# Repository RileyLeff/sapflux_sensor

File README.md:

# Sap Flux Logic Board

An open hardware logic board for experimental heat-pulse sap flux sensors.

Sap flux sensors estimate how water moves through trees by watching heat move
through sapwood. Current sensors are expensive, power-hungry, and not all that accurate.

This repo contains some hardware I'm developing to fix all of that stuff!

## Current Status

The board is real and in-hand. The first revision literally exploded on power-on because I did not know the convention for communicating diode orientation to JLCPCB.

The repo now contains a second revision of the board with some minor improvements to the power layout, and I did not bork the layout confirmation on the second order. The board is working great in the lab!

So far, the beauty and splendor promised in the simulations seems to transfer to real-world situations. I've seen enough to make me confident that:

1. The new measurement theory works, and crushes the old theory. I'm presenting on this at AGU in December 2026!
2. The logic board design works. I don't think it's fully optimal/ready-to-scale yet, but my initial lab testing has convinced me it's sound.

I'll link to my data and AGU presentation when I have them ready for public consumption. In the meantime, you're welcome to check out the hardware here in this repo.

I haven't yet fully deployed in real field conditions, and I imagine there will be some empirical caveats and gotchas to navigate in those deployments. But so far so good!

The main thing to figure out from here is basically: now that we can actually inference the sap flux model accurately, are there variable, empirical features of the measurement that we can solve with better theory or engineering? Empiricism on plants is hard: they're complicated and diverse. The less empiricism we have to do on our estimates, the higher our bandwidth gets.

## What's Going On In Here?

Want to measure how fast water moves through a tree at high frequency? It's useful to know because it connects a tree to nearly all of its environmental conditions. We have a model to measure this and a sensor to provide data for it, but our model is broken in two specific ways:

- The actual probes in the tree get slightly misaligned when you install them, and tiny misalignments produce mega-huge errors.
- The probes work by introducing a heat pulse into the tree and measuring how fast it moves. How much of that movement is attributable to convection (sap flux) versus conduction? Current implementations attribute all variation to convection, which is a bad assumption.

The first problem is massive in magnitude. The second one is smaller (convection does genuinely change more than conduction) but more destructive per unit error because it's deeply confounded with stuff on the tree that you actually want to measure, like water potential or wood density.

This is open hardware that allows me to test my newly derived method for inferring sap flux rates from the raw data: we can't use commercial sensors because they're locked down and they discard most of the raw signal in favor of restrictive summary statistics. I do have a separate project that decompresses those summary statistics into distributions of possible raw measurements, but it's better to just keep the data in the first place.

Since we're already in the business of building custom hardware, we can get the power consumption down and the costs down as well.

## What The Board Does

Here are some design notes:

- 48 thermistor channels through three analog multiplexers.
- One ADS1115 ADC for heat-pulse temperature traces and excitation sensing.
- Support for analog sensor heads with internal 10k half-bridge thermistor setups.
- Shorter, higher-power heat pulses (which flatten out the signal less).
- Up to 120W power output in very short bursts across 8 sensors with ~40-45 ohm heater resistance.
- 24V field power input with protection and a 3.3V buck supply.
- RS-485.
- 32 MB SPI flash.
- I2C EEPROM.
- STM32G0B1 microcontroller target, intended for embedded Rust firmware with
  the [Embassy](https://github.com/embassy-rs/embassy) framework.
- Six layers, KiCad layout, fabbed at JLC.

I put a fairly complex analog mechanism for shutting down the heater on here because I'm worried about the case where a broken sensor in a dead tree starts a forest fire. This is probably the area that could use the most simplification in future revisions. Right now it mostly serves to annoyingly latch my heater shut by accident if the power supply ever blips in a way that the power shutdown doesn't like. I've made some firmware improvements for handling it, but I think the hardware could be improved there.

## Compared With Current Workflows

This one:
- Open, hackable
- <1mW idle power consumption (if you're creative with shutting off the RS-485 transceiver, e.g., a 15-second polling interval)
- Maybe $50/board at small/medium volumes, $20/board at large volumes

Commercial:
- Closed
- \>100mW idle power consumption
- $1000/sensor + $1000+ logger
- More expensive infrastructure to support the greater power consumption

I don't think this is the final sensor topology, but 8x analog sensor heads per board is really nice for testing the method in the lab. I figure I'll make a more integrated, more deployment-friendly design in the future.

## Reproducibility

Atopile is the canonical electrical design source for this board:

- [`elec/main.ato`](elec/main.ato)
- [`elec/ato.yaml`](elec/ato.yaml)
- [`elec/`](elec/)

Note that I found it *really nice* to work with Claude via atopile! I'm still doing the layout by hand, but putting the electrical connectivity in a Python-like language made iteration and review a breeze.

Same with the PCBParts MCP server. I always found navigating parts to be a big barrier between me, the inexperienced hardware fan that fools around with breadboards sometimes, and building a PCB from scratch. Claude is really good at that stuff if you provide good tools.

The KiCad layout is here:

- [`elec/layouts/default/default.kicad_pcb`](elec/layouts/default/default.kicad_pcb)

The shipped fabrication packages are frozen here:

- v0.2 (current, working board): [`releases/sap-flux-adapter-v0.2-2026-06-26/`](releases/sap-flux-adapter-v0.2-2026-06-26/)
- v0.1 (first board; the folder name says v1.1, but the board itself is labeled v0.1): [`releases/sap-flux-adapter-v1.1-shipped-2026-03-21/`](releases/sap-flux-adapter-v1.1-shipped-2026-03-21/)

For more detail, see [`docs/reproducibility.md`](docs/reproducibility.md). Note that it's a Claude-written document. I suggest pointing your LLM agent at the repo to inspect the guts of it. This README is written by hand (by Riley) but the rest of the repo is a Claude party.

## Internal Links (Claude's Docs)

- Specs: [`docs/specs.md`](docs/specs.md)
- Reproducibility notes: [`docs/reproducibility.md`](docs/reproducibility.md)
- Design history: [`docs/design-history/`](docs/design-history/)
- Shipped releases: [v0.2](releases/sap-flux-adapter-v0.2-2026-06-26/), [v0.1](releases/sap-flux-adapter-v1.1-shipped-2026-03-21/)

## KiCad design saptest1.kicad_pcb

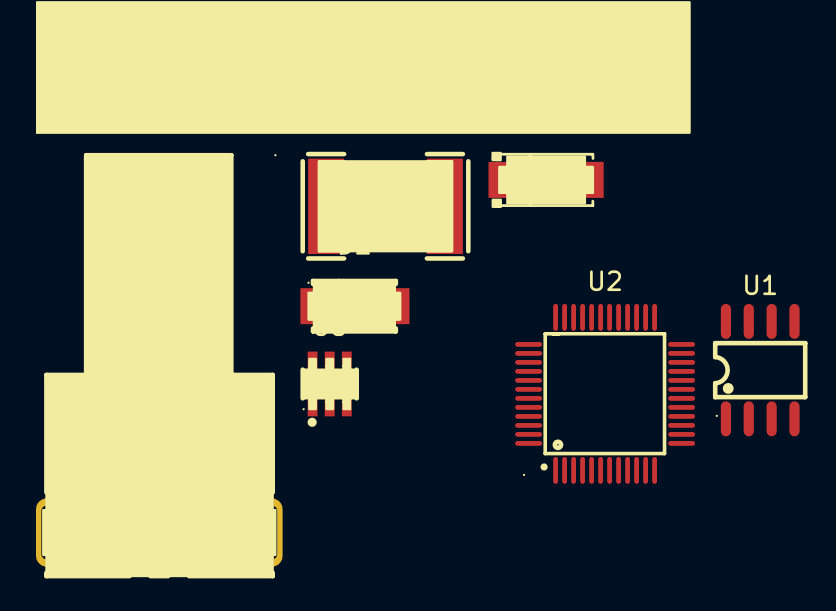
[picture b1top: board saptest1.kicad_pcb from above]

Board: 2 copper layers, 8 parts (0 on the bottom side), 4 nets, no tracks yet.

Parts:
D1: SS36; SMA_L4.3-W2.6-LS5.2-RD
D2: SMAJ30A_C698947; SMA_L4.5-W2.6-LS5.1-RD
F1: 2920L110/60MR; F2920
J1: M8-P4A-GPL_M8-JD; CONN-TH_M8-P4A-GPL-M8-JD
U1: CAT24C32WI-GT3; SOIC-8_L5.0-W4.0-P1.27-LS6.0-BL
U2: STM32G0B1CBT6; LQFP-48_L7.0-W7.0-P0.50-LS9.0-BL
U3: KF2EDGV-3_5-10P; CONN-TH_10P-P3.50_KF2EDGV-3.5-10P
U5: LMR14006YDDCR; TSOT-23-6_L2.9-W1.6-P0.95-LS2.8-BL

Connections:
+24V Protected: D1.1 (K), D2.1
GND: D2.2, J1.3
unnamed: D1.2 (A), F1.2
unnamed: F1.1, J1.1

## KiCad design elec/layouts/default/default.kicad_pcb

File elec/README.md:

# Sap Flux Adapter Electronics

This directory contains the Atopile source for the sap flux adapter board.
Atopile is the canonical electrical design for the shipped prototype.

## Entry Point

- `main.ato` defines the top-level `SapFluxAdapter` module.
- `ato.yaml` defines the `default` build.
- `layouts/default/default.kicad_pcb` is the hand-routed KiCad layout that was
  fabricated by JLCPCB.

## Build

```bash
ato build
```

Run from this directory.

Be careful with rebuilds: the KiCad PCB includes hand placement, routing,
board-art, and late manufacturing fixes. For the board that was physically
fabricated, use the frozen release package in
`../releases/sap-flux-adapter-v1.1-shipped-2026-03-21/`.

## Tooling

This design was built with Atopile and KiCad. `pcbparts` was used heavily for
part discovery and package/footprint work while learning hardware design.

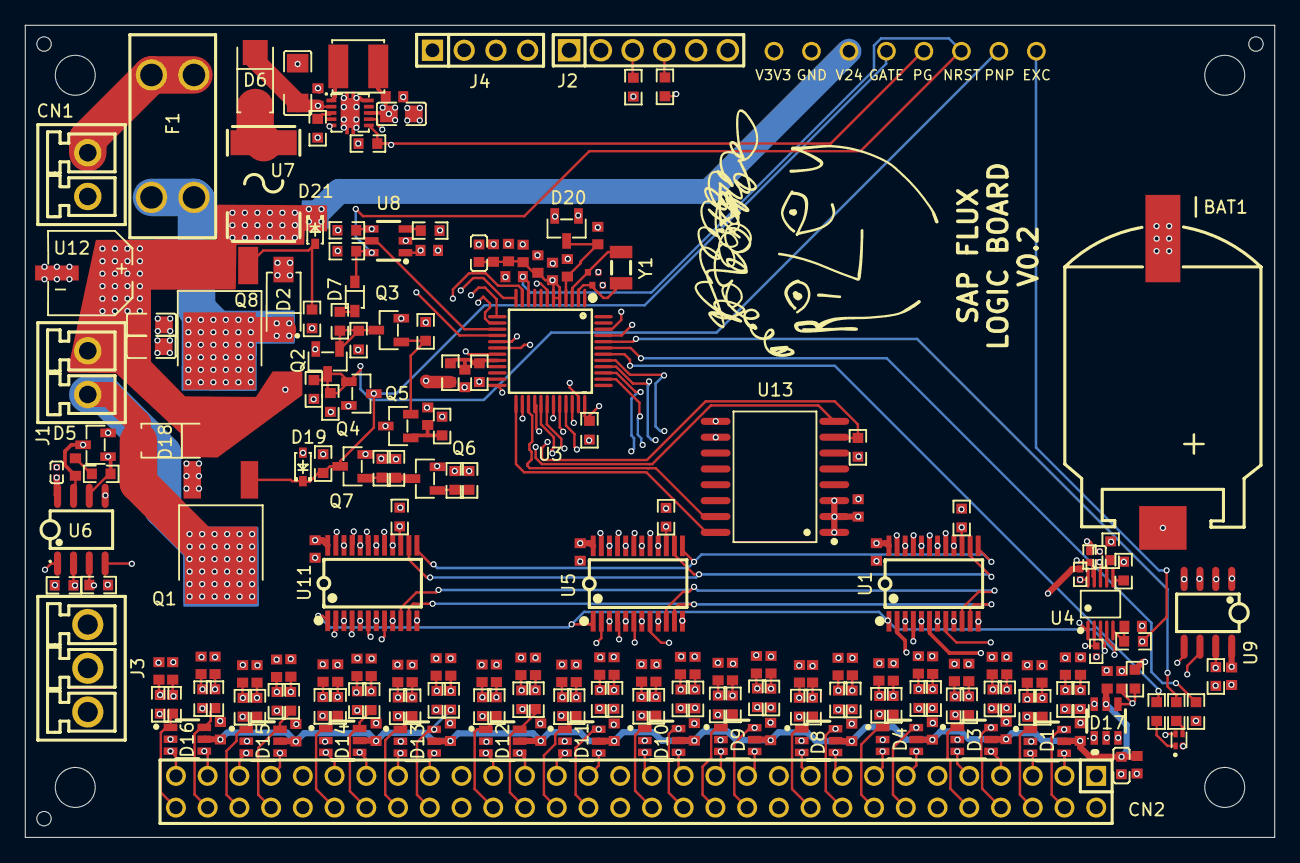
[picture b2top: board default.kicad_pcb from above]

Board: 6 copper layers, 100.0 x 65.0 mm, 248 parts (0 on the bottom side), 169 nets.

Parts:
BAT1: BAT-SMD_BS-CR2032-8
C1: C1206
C2, C4, C5, C6, C8, C9, C10, C12, C13, C14, C15, C16, C17, C18, C19, C20, C21, C23, C24, C25, C26, C27, C28, C29, C30, C31, C32, C33, C34, C35, C36, C37, C38, C39, C40, C41, C42, C43, C44, C45, C46, C47, C48, C49, C50, C51, C52, C53, C54, C55, C56, C57, C58, C59, C60, C61, C62, C63, C64, C65, C66, C67, C68, C69, C70, C71, C72, C73, C74, C75, C76, C77, C78, C79, C80, C81, C82, C83, C84, C85, C86, C87, C88: C0603
C3, C7, C91: C0805
C11, C22: 100nF ±10%; C0402
C89, C90: C0402
CN1: CONN-TH_P3.50_KF2EDGV-3.5-2P
CN2: HDR-TH_60P-P2.54-V-M-R2-C30-S2.54
D1, D3, D4, D8, D9, D10, D11, D12, D13, D14, D15, D16, D17: SOT-23-6_L2.9-W1.6-P0.95-LS2.8-BR
D2, D18: SMA_L4.3-W2.6-LS5.0-RD
D5, D20: SOT-23-3_L2.9-W1.3-P1.90-LS2.4-BR
D6: SMA_L4.3-W2.6-LS5.2-RD
D7: SOD-323_L1.8-W1.3-LS2.5-RD
D19, D21: SOD-323_L1.7-W1.3-LS2.6-RD
EXC: TestPoint_Pad_D1.5mm
F1: FUSE-TH_4P-L16.0-W6.7
GATE: TestPoint_Pad_D1.5mm
GND: TestPoint_Pad_D1.5mm
H1, H2, H3, H4: MountingHole_3.2mm_M3
J1: CONN-TH_P3.50_KF2EDGV-3.5-2P
J2: HDR-TH_6P-P2.54-V-M-1
J3: CONN-TH_3P-P3.50_KF2EDGV-3.5-3P
J4: HDR-TH_4P-P2.54-V-M
L1: IND-SMD_L4.0-W4.0
L2, L3: L0603
NRST: TestPoint_Pad_D1.5mm
PG: TestPoint_Pad_D1.5mm
PNP: TestPoint_Pad_D1.5mm
Q1: TO-252-2_L6.6-W6.2-P4.57-LS10.1-BR-CW
Q2, Q3, Q4, Q5, Q6, Q7: SOT-23-3_L2.9-W1.3-P1.90-LS2.4-BR
Q8: TO-252-2_L6.5-W5.6-P4.60-LS9.7-BR
R1: R0603
R2, R21, R26, R33, R74, R75, R76, R79, R82, R85: 10kΩ ±1%; R0603
R3, R4, R5: 10kΩ ±1%; R0402
R6, R7, R8, R9, R10, R11, R12, R13, R14, R15, R20, R24, R35, R36, R37, R38, R39, R40, R41, R42, R43, R44, R45, R46, R47, R48, R49, R50, R51, R52, R53, R54, R55, R56, R57, R58, R59, R60, R61, R62, R63, R64, R65, R66, R67, R68, R69, R70, R71, R72, R73, R77, R78: 1kΩ ±1%; R0603
R16: 270Ω ±1%; R0603
R17, R18: 68kΩ ±1%; R0603
R19: 120Ω ±1%; R0603
R22: 11kΩ ±1%; R0603
R23, R27, R28, R29, R81: 100kΩ ±1%; R0603
R25, R34: 1MΩ ±1%; R0603
R30: 220Ω ±1%; R0603
R31: 200Ω ±1%; R0603
R32: 680Ω ±1%; R0603
R80: 10MΩ ±1%; R0603
R83: 2MΩ ±1%; R0603
R84, R86, R88: 4.7MΩ ±1%; R0603
R87: 470kΩ ±1%; R0603
TH1, TH2, TH3: ToolingHole_1.152mm
U1, U5, U11: TSSOP-24_L7.8-W4.4-P0.65-LS6.4-BL
U2: VSON-10_L3.0-W3.0-P0.50-TL-EP
U3: LQFP-48_L7.0-W7.0-P0.50-LS9.0-BL
U4: MSOP-10_L3.0-W3.0-P0.50-LS5.0-BL
U6, U9: SOIC-8_L5.0-W4.0-P1.27-LS6.0-BL
U7: F2920
U8: SOT-23-6_L2.9-W1.6-P0.95-LS2.8-BR
U10: LED-SMD_4P-L1.2-W1.2_BR
U12: CAP-SMD_BD6.3-L6.6-W6.6-LS7.2-FD
U13: SOIC-16_L10.3-W7.5-P1.27-LS10.3-BL
V3V3, V24: TestPoint_Pad_D1.5mm
Y1: FC-135R_L3.2-W1.5

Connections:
1: L1.1, U2.1
2: BAT1.2, D20.2
3: J2.3, R78.2
4: J2.4, R77.2
6: R72.1, U4.6
7: R73.1, U4.7
10: U1.10, U3.38, U5.10, U11.10
11: U1.11, U3.39, U5.11, U11.11
13: U1.13, U3.41, U5.13, U11.13
14: U1.14, U3.40, U5.14, U11.14
ALERT_RDY: R3.1, U3.19, U4.2
B: R30.1, U10.3
D: D19.1, GATE.1, Q1.1, Q4.3, Q7.3, R84.2
DELAY_M_RST: R22.1, U8.3
EXC: C20.1, CN2.2, CN2.22, CN2.42, D17.4, EXC.1, R15.1, R16.2
G: R31.1, U10.4
GND: BAT1.1, C1.2, C2.2, C3.2, C4.2, C5.2, C6.2, C7.2, C8.2, C9.2, C10.2, C11.2, C12.2, C13.2, C14.2, C15.2, C16.2, C17.2, C18.2, C19.2, C20.2, C22.2, C23.2, C24.2, C25.2, C26.2, C27.2, C28.2, C29.2, C30.2, C31.2, C32.2, C33.2, C34.2, C35.2, C36.2, C37.2, C38.2, C39.2, C40.2, C41.2, C42.2, C43.2, C44.2, C45.2, C46.2, C47.2, C48.2, C49.2, C50.2, C51.2, C52.2, C53.2, C54.2, C55.2, C56.2, C57.2, C58.2, C59.2, C60.2, C61.2, C62.2, C63.2, C64.2, C65.2, C66.2, C67.2, C68.2, C69.2, C70.2, C71.2, C72.2, C73.2, C74.2, C75.2, C76.2, C77.2, C78.2, C79.2, C80.2, C81.2, C82.2, C83.2, C84.2, C85.2, C86.2, C87.2, C88.2, C89.2, C90.2, C91.2, CN1.2, CN2.1, CN2.11, CN2.12, CN2.21, CN2.31, CN2.32, CN2.41, CN2.51, CN2.52, D1.2, D2.2, D3.2, D4.2, D5.2, D8.2, D9.2, D10.2, D11.2, D12.2, D13.2, D14.2, D15.2, D16.2, D17.1, D17.2, D17.3, D17.6, D19.2, GND.1, J2.1, J2.2, J3.3, J4.4, Q1.3, Q3.2, Q4.2, Q6.2, Q7.2, R1.2, R2.2, R17.2, R18.2, R22.2, R25.2, R26.2, R28.2, R72.2, R73.2, R81.2, R83.2, R87.2, R88.2, U1.12, U2.5, U2.10, U2.11, U3.7, U4.1, U4.3, U5.12, U6.5, U8.2, U9.1, U9.2, U9.3, U9.4, U11.12, U12.2, U13.10
ILIM: R1.1, U2.3
NRST: C9.1, D7.1, NRST.1, R27.1, U3.10, U8.6
PC15_OSC32_OUT: C90.1, U3.3, Y1.2
PGOOD: PG.1, R34.1, R85.1, U2.6, U3.31
Q_REV_GATE: D21.2, Q8.1, R88.1
R: R32.1, U10.1
RS485_TERM: C21.1, R19.2
RX: U3.14, U6.1
SCL: R4.1, R77.1, U3.45, U4.10, U9.6
SDA: R5.1, R78.1, U3.46, U4.9, U9.5
TX: U3.13, U6.4
V3V3: C3.1, C4.1, C5.1, C11.1, C22.1, C23.1, C69.1, C70.1, C71.1, C85.1, J4.1, L1.2, L2.1, L3.1, Q2.2, R3.2, R4.2, R5.2, R27.2, R29.2, R33.2, R74.2, R75.2, R76.2, R79.2, R85.2, U1.24, U2.8, U4.8, U5.24, U6.8, U8.1, U9.8, U10.2, U11.24, U13.1, U13.2, U13.3, U13.9, V3V3.1
V3V3_TVS: C68.1, C72.1, C73.1, C74.1, C75.1, C76.1, C77.1, C78.1, C79.1, C80.1, C81.1, C82.1, C83.1, C84.1, D1.5, D3.5, D4.5, D8.5, D9.5, D10.5, D11.5, D12.5, D13.5, D14.5, D15.5, D16.5, D17.5, L3.2
V24_BUCK: C1.1, C2.1, D6.1, U2.2, U2.7
V24_FUSED_RAW: D2.1, F1.2, F1.3, Q8.3
V24_PROT: C7.1, C91.1, D18.1, D21.1, J1.1, Q8.2, R80.1, R84.1, R86.1, U7.1, U12.1, V24.1
V24_RAW: CN1.1, F1.1, F1.4
VDDA_FILT: C8.1, C10.1, C24.1, C25.1, C88.1, D20.1, L2.2, U3.5, U3.6
WP: R33.1, U3.34, U9.7
Z: U1.1, U4.4, U5.1, U11.1
arm_node: C28.1, Q5.1, R34.2
blue: R30.2, U3.44
cs: R79.1, U3.24, U13.7
ctrl_gate_node: Q6.1, R81.1, R82.2
d_iso_anode_node: D7.2, R21.1
de: R17.1, U3.12, U6.3
done: R28.1, U3.16, U8.4
driver_gate_node: Q6.3, Q7.1, R80.2, R83.1
excitation_gpio: R16.1, U3.30
fb_out_node: Q5.3, R23.2
gate_drive: R82.1, U3.28
gpio_pa6: J2.5, U3.17
gpio_pa7: J2.6, U3.18
green: R31.2, U3.43
heater_lo: D18.2, J1.2, Q1.2
latch_base_node: Q3.1, Q5.2, R25.1
mcu-1: C86.1, C87.1, D20.3, U3.4
mcu-1-1: C89.1, U3.2, Y1.1
miso: U3.26, U13.8
mosi: U3.27, U13.15
mux_en_a: R74.1, U1.15, U3.29
mux_en_b: R75.1, U3.32, U5.15
mux_en_c: R76.1, U3.33, U11.15
n_re: R18.1, U3.11, U6.2
pnp_base_node: Q2.1, Q3.3, R21.2, R29.1
pnp_coll_node: PNP.1, Q2.3, Q4.1, R23.1, R26.1
prot_1: C12.1, R6.2, U1.8
prot_2: C13.1, R7.2, U1.9
prot_3: C14.1, R8.2, U1.6
prot_4: C15.1, R9.2, U1.7
prot_5: C16.1, R10.2, U1.4
prot_6: C17.1, R11.2, U1.5
prot_7: C18.1, R12.2, U1.2
prot_8: C26.1, R13.2, U1.3
prot_9: C27.1, R14.2, U1.17
prot_10: C29.1, R20.2, U1.16
prot_11: C30.1, R24.2, U1.19
prot_12: C31.1, R35.2, U1.18
prot_13: C32.1, R36.2, U1.21
prot_14: C33.1, R37.2, U1.20
prot_15: C34.1, R38.2, U1.23
prot_16: C35.1, R39.2, U1.22
prot_17: C36.1, R40.2, U5.8
prot_18: C37.1, R41.2, U5.9
prot_19: C38.1, R42.2, U5.6
prot_20: C39.1, R43.2, U5.7
prot_21: C40.1, R44.2, U5.4
prot_22: C41.1, R45.2, U5.5
prot_23: C42.1, R46.2, U5.2
prot_24: C43.1, R47.2, U5.3
prot_25: C44.1, R48.2, U5.17
prot_26: C45.1, R49.2, U5.16
prot_27: C46.1, R50.2, U5.19
prot_28: C47.1, R51.2, U5.18
prot_29: C48.1, R52.2, U5.21
prot_30: C49.1, R53.2, U5.20
prot_31: C50.1, R54.2, U5.23
prot_32: C51.1, R55.2, U5.22
prot_33: C52.1, R56.2, U11.8
prot_34: C53.1, R57.2, U11.9
prot_35: C54.1, R58.2, U11.6
prot_36: C55.1, R59.2, U11.7
prot_37: C56.1, R60.2, U11.4
prot_38: C57.1, R61.2, U11.5
prot_39: C58.1, R62.2, U11.2
prot_40: C59.1, R63.2, U11.3
prot_41: C60.1, R64.2, U11.17
prot_42: C61.1, R65.2, U11.16
prot_43: C62.1, R66.2, U11.19
prot_44: C63.1, R67.2, U11.18
prot_45: C64.1, R68.2, U11.21
prot_46: C65.1, R69.2, U11.20
prot_47: C66.1, R70.2, U11.23
prot_48: C67.1, R71.2, U11.22
prot_exc: C19.1, R15.2, U4.5
ptc_out: D6.2, U7.2
red: R32.2, U3.42
rs485_a_P: D5.1, J3.1, R19.1, U6.6
rs485_b_N: C21.2, D5.3, J3.2, U6.7
sck: U3.25, U13.16
swclk: J4.3, R2.1, U3.36
swdio: J4.2, U3.35
therm_1: CN2.3, D1.4, R6.1
therm_2: CN2.4, D1.6, R7.1
therm_3: CN2.5, D1.3, R8.1
therm_4: CN2.6, D1.1, R9.1
therm_5: CN2.7, D3.4, R10.1
therm_6: CN2.8, D3.6, R11.1
therm_7: CN2.9, D3.3, R12.1
therm_8: CN2.10, D3.1, R13.1
therm_9: CN2.13, D4.4, R14.1
therm_10: CN2.14, D4.6, R20.1
therm_11: CN2.15, D4.3, R24.1
therm_12: CN2.16, D4.1, R35.1
therm_13: CN2.17, D8.4, R36.1
therm_14: CN2.18, D8.6, R37.1
therm_15: CN2.19, D8.3, R38.1
therm_16: CN2.20, D8.1, R39.1
therm_17: CN2.23, D9.4, R40.1
therm_18: CN2.24, D9.6, R41.1
therm_19: CN2.25, D9.3, R42.1
therm_20: CN2.26, D9.1, R43.1
therm_21: CN2.27, D10.4, R44.1
therm_22: CN2.28, D10.6, R45.1
therm_23: CN2.29, D10.3, R46.1
therm_24: CN2.30, D10.1, R47.1
therm_25: CN2.33, D11.4, R48.1
therm_26: CN2.34, D11.6, R49.1
therm_27: CN2.35, D11.3, R50.1
therm_28: CN2.36, D11.1, R51.1
therm_29: CN2.37, D12.4, R52.1
therm_30: CN2.38, D12.6, R53.1
therm_31: CN2.39, D12.3, R54.1
therm_32: CN2.40, D12.1, R55.1
therm_33: CN2.43, D13.4, R56.1
therm_34: CN2.44, D13.6, R57.1
therm_35: CN2.45, D13.3, R58.1
therm_36: CN2.46, D13.1, R59.1
therm_37: CN2.47, D14.4, R60.1
therm_38: CN2.48, D14.6, R61.1
therm_39: CN2.49, D14.3, R62.1
therm_40: CN2.50, D14.1, R63.1
therm_41: CN2.53, D15.4, R64.1
therm_42: CN2.54, D15.6, R65.1
therm_43: CN2.55, D15.3, R66.1
therm_44: CN2.56, D15.1, R67.1
therm_45: CN2.57, D16.4, R68.1
therm_46: CN2.58, D16.6, R69.1
therm_47: CN2.59, D16.3, R70.1
therm_48: CN2.60, D16.1, R71.1
vmon_mid: C6.1, R86.2, R87.1, U3.20
wake: U3.15, U8.5

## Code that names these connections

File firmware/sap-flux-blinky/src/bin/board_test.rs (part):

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    let watchdog_done = Output::new(p.PA5, Level::Low, Speed::Low);
    spawner.spawn(watchdog_keepalive(watchdog_done).unwrap());
    let mut excitation = Output::new(p.PC6, Level::Low, Speed::Low);
    let mut mux_en_a = Output::new(p.PA9, Level::High, Speed::Low);
    let mut mux_en_b = Output::new(p.PA10, Level::High, Speed::Low);
    let mut mux_en_c = Output::new(p.PA11, Level::High, Speed::Low);
    let mut mux_s0 = Output::new(p.PD0, Level::Low, Speed::Low);
    let mut mux_s1 = Output::new(p.PD1, Level::Low, Speed::Low);
    let mut mux_s2 = Output::new(p.PD2, Level::Low, Speed::Low);
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    let mut led_red = Output::new(p.PB3, Level::High, Speed::Low);
    let mut led_green = Output::new(p.PB4, Level::High, Speed::Low);
    let mut led_blue = Output::new(p.PB5, Level::High, Speed::Low);
    let pgood = Input::new(p.PC7, Pull::None);
    let mut v24_monitor = p.PB1;
    let mut adc1 = Adc::new(p.ADC1);

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    uart_config.baudrate = 115_200;
    let uart = Uart::new_blocking(p.USART2, p.PA3, p.PA2, uart_config).unwrap();
    let de = Output::new(p.PA1, Level::Low, Speed::Low);
    let n_re = Output::new(p.PA0, Level::Low, Speed::Low);
    let mut rs485 = Rs485 { uart, de, n_re };

    let mut i2c_config = I2cConfig::default();
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    mux_s3: &mut Output<'_>,
) {
    rs485
        .line("Therm1 known-resistor probe: expects resistor J2 pin2(EXC) to pin3(T1)")
        .await;

    excitation.set_low();
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
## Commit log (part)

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2026-02-26 current state
2026-05-01 Polish repo for shipped sap flux board
2026-06-22 Checkpoint v0.2 board bringup state
2026-06-22 Migrate layout toward Atopile 0.15
2026-06-22 Own mechanical footprints in Atopile
2026-06-22 Increase buck PFM current limit
2026-06-24 Checkpoint v0.2 layout reroute
2026-06-24 Prepare flash no-connect nets
2026-06-24 Propagate flash no-connect nets to layout
2026-06-24 Add XFCN fuse footprint library
2026-06-25 Checkpoint idle-power board edits
2026-06-25 Propagate idle-power resistor picks to layout
2026-06-25 Reduce RS485 boot pulldown current
2026-06-25 Checkpoint manual silkscreen layout edits
2026-06-25 Move front logo polygons back to silkscreen
2026-06-26 Preserve v0.2 layout silkscreen edits
2026-06-26 Fix v0.2 source issues
2026-06-26 Propagate v0.2 source fixes to board
2026-06-26 Restore KiCad 10 board syntax
2026-06-26 Add final orientation markings
2026-06-26 Package v0.2 manufacturing release
2026-06-26 Substitute stocked resistors in v0.2 BOM

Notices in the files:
parts and their libraries:
CONN-TH_M8-P4A-GPL-M8-JD footprint
